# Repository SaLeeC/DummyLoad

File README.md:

# DummyLoad
Dummy Load with monitoring system

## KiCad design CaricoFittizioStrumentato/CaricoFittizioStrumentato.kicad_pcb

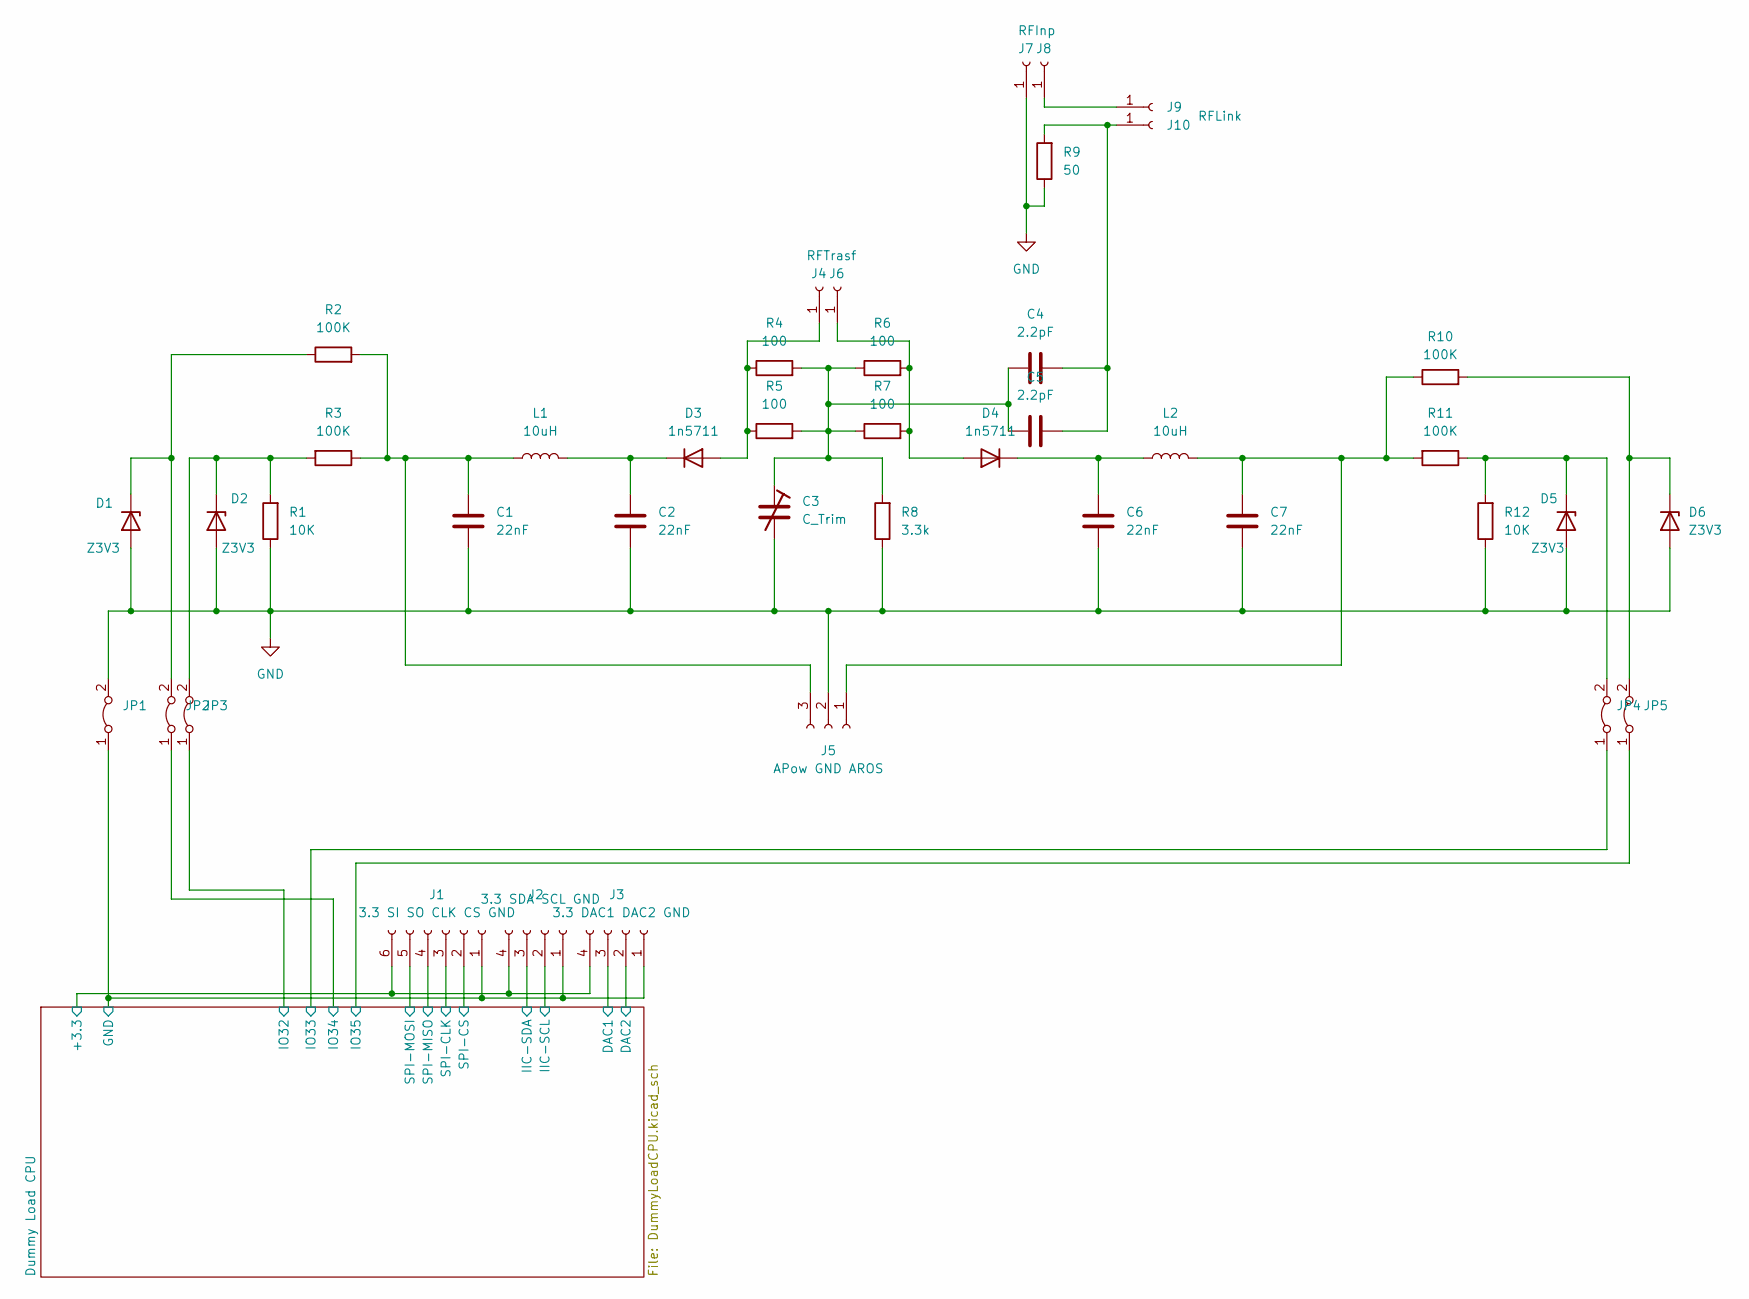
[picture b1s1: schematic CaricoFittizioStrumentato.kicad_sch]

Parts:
C1, C2, C6, C7: 22nF; R_1206_3216Metric
C3: C_Trim; GZC10100
C4, C5: 2.2pF; R_1206_3216Metric
D1, D2, D5, D6: Z3V3; D_1210_3225Metric
D3, D4: 1n5711; D_A-405_P10.16mm_Horizontal
J1: 3.3 SI SO CLK CS GND; PinSocket_1x06_P2.54mm_Vertical
J2: 3.3 SDA SCL GND; PinSocket_1x04_P2.54mm_Vertical
J3: 3.3 DAC1 DAC2 GND; PinSocket_1x04_P2.54mm_Vertical
J4, J8, J9: TestPoint_Loop_D1.80mm_Drill1.0mm_Beaded
J5: APow GND AROS; PinSocket_1x03_P2.54mm_Vertical
J6: RFTrasf; TestPoint_Loop_D1.80mm_Drill1.0mm_Beaded
J7: RFInp; TestPoint_Loop_D1.80mm_Drill1.0mm_Beaded
J10: RFLink; TestPoint_Loop_D1.80mm_Drill1.0mm_Beaded
JP1, JP2, JP3, JP4, JP5: SolderJumper-2_P1.3mm_Bridged_RoundedPad1.0x1.5mm
L1, L2: 10uH; L_1206_3216Metric
R1, R12: 10K; R_1206_3216Metric
R2, R3, R10, R11: 100K; R_1206_3216Metric
R4, R5, R6, R7: 100; R_2512_6332Metric
R8: 3.3k; R_1206_3216Metric
R9: 50; High Power RF Resistor 001

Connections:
/Dummy Load CPU/+3.3: J1.6, J2.4, J3.4; also elsewhere on the board
/Dummy Load CPU/DAC1: J3.3; also elsewhere on the board
/Dummy Load CPU/DAC2: J3.2; also elsewhere on the board
/Dummy Load CPU/IIC-SCL: J2.2; also elsewhere on the board
/Dummy Load CPU/IIC-SDA: J2.3; also elsewhere on the board
/Dummy Load CPU/IO32: JP3.1 (A); also elsewhere on the board
/Dummy Load CPU/IO33: JP4.1 (A); also elsewhere on the board
/Dummy Load CPU/IO34: JP2.1 (A); also elsewhere on the board
/Dummy Load CPU/IO35: JP5.1 (A); also elsewhere on the board
/Dummy Load CPU/SPI-CLK: J1.3; also elsewhere on the board
/Dummy Load CPU/SPI-CS: J1.2; also elsewhere on the board
/Dummy Load CPU/SPI-MISO: J1.4; also elsewhere on the board
/Dummy Load CPU/SPI-MOSI: J1.5; also elsewhere on the board
unnamed: C1.2, J5.3, L1.1, R2.2, R3.1
unnamed: C2.2, D3.1 (K), L1.2
unnamed: C3.1, C3.3, C4.1, C5.1, R4.2, R5.2, R6.1, R7.1, R8.2
unnamed: C4.2, C5.2, J10.1, R9.2
unnamed: C6.2, D4.1 (K), L2.1
unnamed: C7.2, J5.1, L2.2, R10.1, R11.2
unnamed: D1.1 (K), JP2.2 (B), R2.1
unnamed: D2.1 (K), JP3.2 (B), R1.2, R3.2
unnamed: D3.2 (A), J4.1, R4.1, R5.1
unnamed: D4.2 (A), J6.1, R6.2, R7.2
unnamed: D5.1 (K), JP4.2 (B), R11.1, R12.2
unnamed: D6.1 (K), JP5.2 (B), R10.2
unnamed: J8.1, J9.1

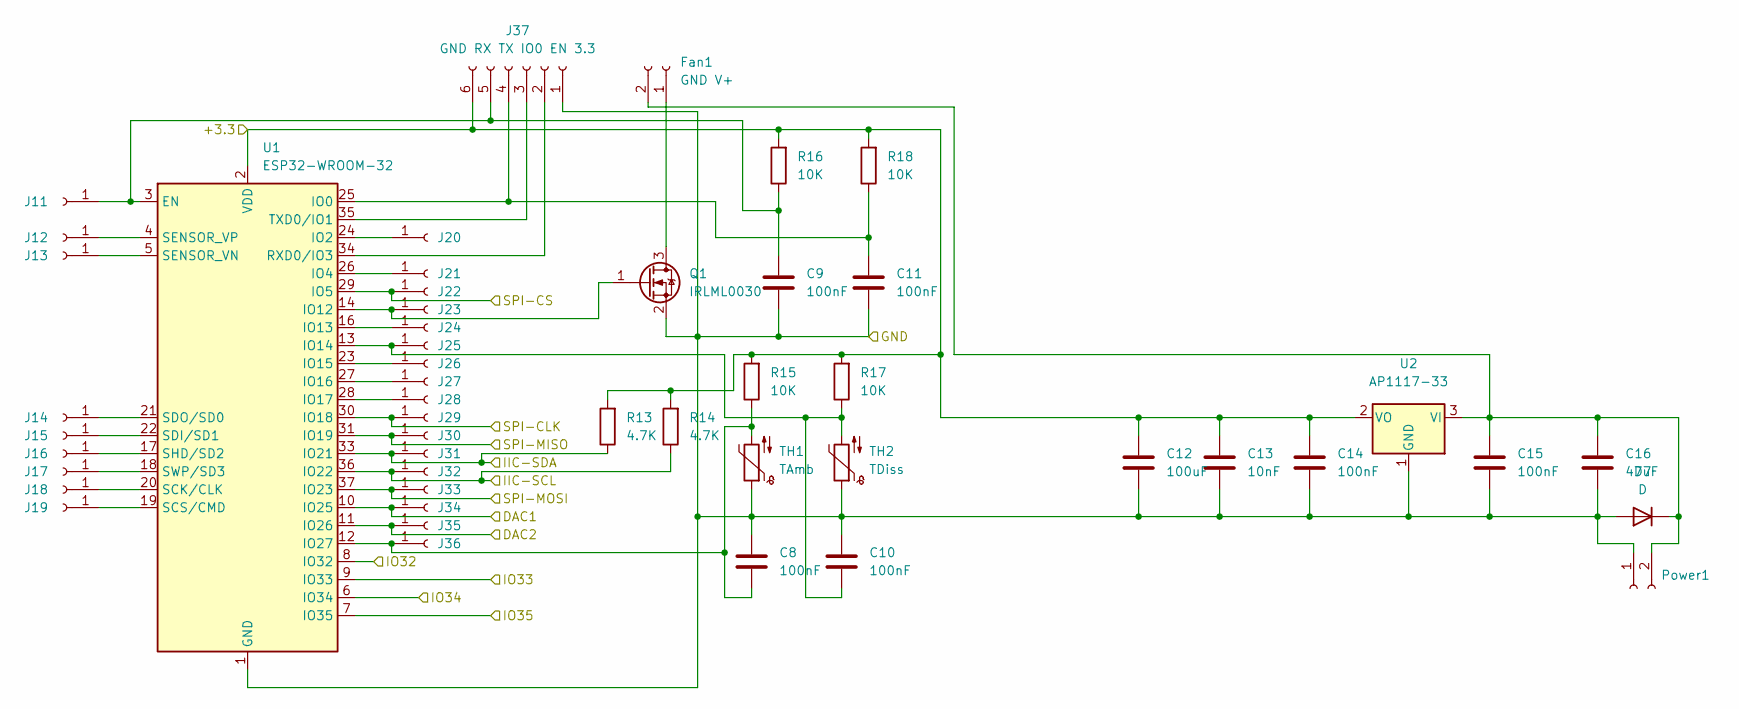
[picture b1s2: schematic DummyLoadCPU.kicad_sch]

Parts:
C8, C9, C10, C11, C14, C15: 100nF; R_1206_3216Metric
C12: 100uF; R_1206_3216Metric
C13: 10nF; R_1206_3216Metric
C16: 47uF; R_1206_3216Metric
D7: D; D_1812_4532Metric
Fan1: GND V+; PinHeader_1x02_P2.54mm_Vertical
J11, J12, J13, J14, J15, J16, J17, J18, J19, J20, J21, J22, J23, J24, J25, J26, J27, J28, J29, J30, J31, J32, J33, J34, J35, J36: PinHeader_1x01_P1.27mm_Vertical
J37: GND RX TX IO0 EN 3.3; PinSocket_1x06_P2.54mm_Vertical
Power1: PinHeader_1x02_P2.54mm_Vertical
Q1: IRLML0030; SOT-23
R13, R14: 4.7K; R_1206_3216Metric
R15, R16, R17, R18: 10K; R_1206_3216Metric
TH1: TAmb; PinSocket_1x02_P2.54mm_Vertical
TH2: TDiss; PinSocket_1x02_P2.54mm_Vertical
U1: ESP32-WROOM-32
U2: AP1117-33; SOT-223-3_TabPin2

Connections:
/Dummy Load CPU/+3.3: C12.2, C13.2, C14.2, J37.6, R13.2, R14.2, R15.2, R16.2, R17.2, R18.2, U1.2 (VDD), U2.2 (VO); also elsewhere on the board
/Dummy Load CPU/DAC1: J34.1, U1.10 (IO25); also elsewhere on the board
/Dummy Load CPU/DAC2: J35.1, U1.11 (IO26); also elsewhere on the board
/Dummy Load CPU/IIC-SCL: J32.1, R14.1, U1.36 (IO22); also elsewhere on the board
/Dummy Load CPU/IIC-SDA: J31.1, R13.1, U1.33 (IO21); also elsewhere on the board
/Dummy Load CPU/IO32: U1.8 (IO32); also elsewhere on the board
/Dummy Load CPU/IO33: U1.9 (IO33); also elsewhere on the board
/Dummy Load CPU/IO34: U1.6 (IO34); also elsewhere on the board
/Dummy Load CPU/IO35: U1.7 (IO35); also elsewhere on the board
/Dummy Load CPU/SPI-CLK: J29.1, U1.30 (IO18); also elsewhere on the board
/Dummy Load CPU/SPI-CS: J22.1, U1.29 (IO5); also elsewhere on the board
/Dummy Load CPU/SPI-MISO: J30.1, U1.31 (IO19); also elsewhere on the board
/Dummy Load CPU/SPI-MOSI: J33.1, U1.37 (IO23); also elsewhere on the board
unnamed: C8.1, J36.1, R15.1, TH1.2, U1.12 (IO27)
unnamed: C9.2, J11.1, J37.5, R16.1, U1.3 (EN)
unnamed: C10.1, J25.1, R17.1, TH2.2, U1.13 (IO14)
unnamed: C11.2, J37.4, R18.1, U1.25 (IO0)
unnamed: Fan1.1, Q1.3 (D)
unnamed: C15.2, C16.2, D7.1 (K), Fan1.2, Power1.2, U2.3 (VI)
unnamed: J12.1, U1.4 (SENSOR_VP)
unnamed: J13.1, U1.5 (SENSOR_VN)
unnamed: J14.1, U1.21 (SDO/SD0)
unnamed: J15.1, U1.22 (SDI/SD1)
unnamed: J16.1, U1.17 (SHD/SD2)
unnamed: J17.1, U1.18 (SWP/SD3)
unnamed: J18.1, U1.20 (SCK/CLK)
unnamed: J19.1, U1.19 (SCS/CMD)
unnamed: J20.1, U1.24 (IO2)
unnamed: J21.1, U1.26 (IO4)
unnamed: J23.1, Q1.1 (G), U1.14 (IO12)
unnamed: J24.1, U1.16 (IO13)
unnamed: J26.1, U1.23 (IO15)
unnamed: J27.1, U1.27 (IO16)
unnamed: J28.1, U1.28 (IO17)
unnamed: J37.2, U1.34 (RXD0/IO3)
unnamed: J37.3, U1.35 (TXD0/IO1)

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
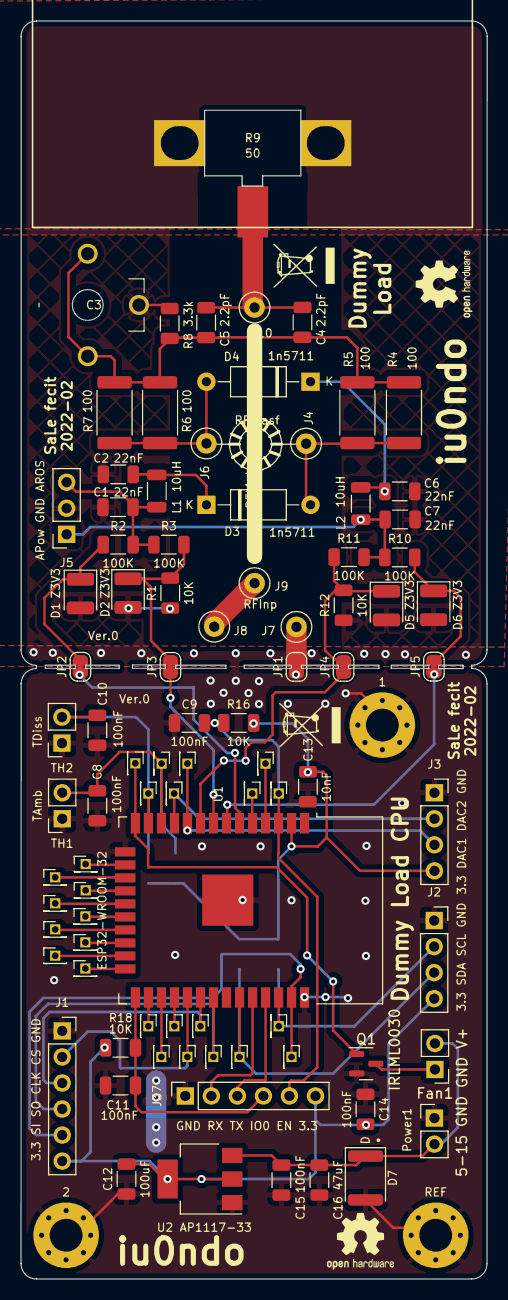
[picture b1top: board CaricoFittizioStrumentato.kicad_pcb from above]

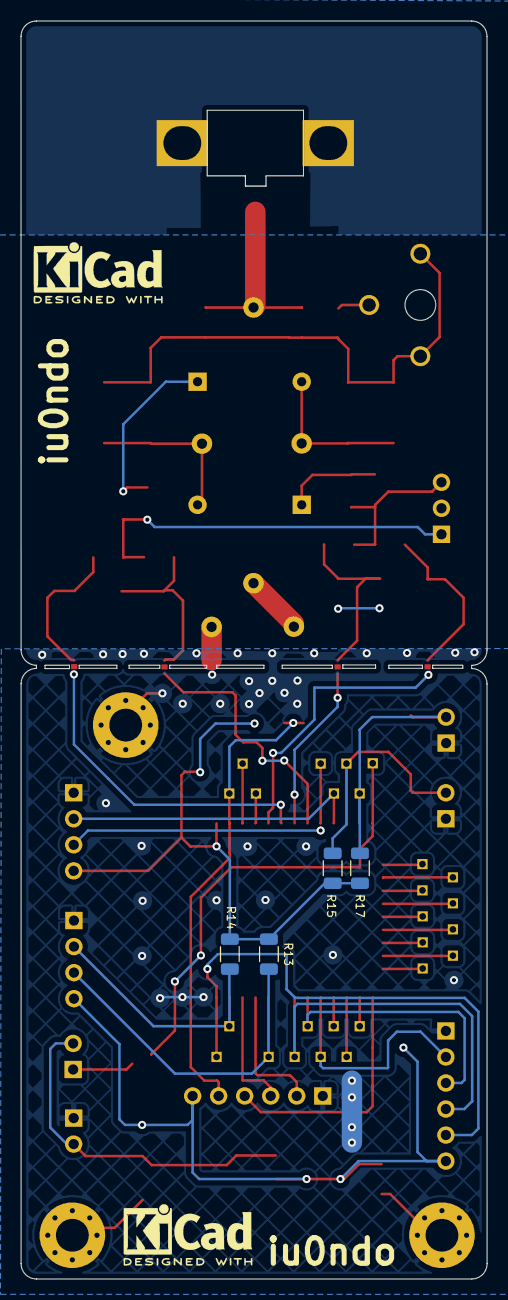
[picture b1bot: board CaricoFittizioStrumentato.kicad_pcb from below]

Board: 2 copper layers, 45.5 x 122.8 mm, 96 parts (4 on the bottom side), 50 nets.

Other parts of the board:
1, 2: MountingHole_3.2mm_M3_Pad_Via
 : ToroCoil Solo Graf
REF : MountingHole_3.2mm_M3_Pad_Via
